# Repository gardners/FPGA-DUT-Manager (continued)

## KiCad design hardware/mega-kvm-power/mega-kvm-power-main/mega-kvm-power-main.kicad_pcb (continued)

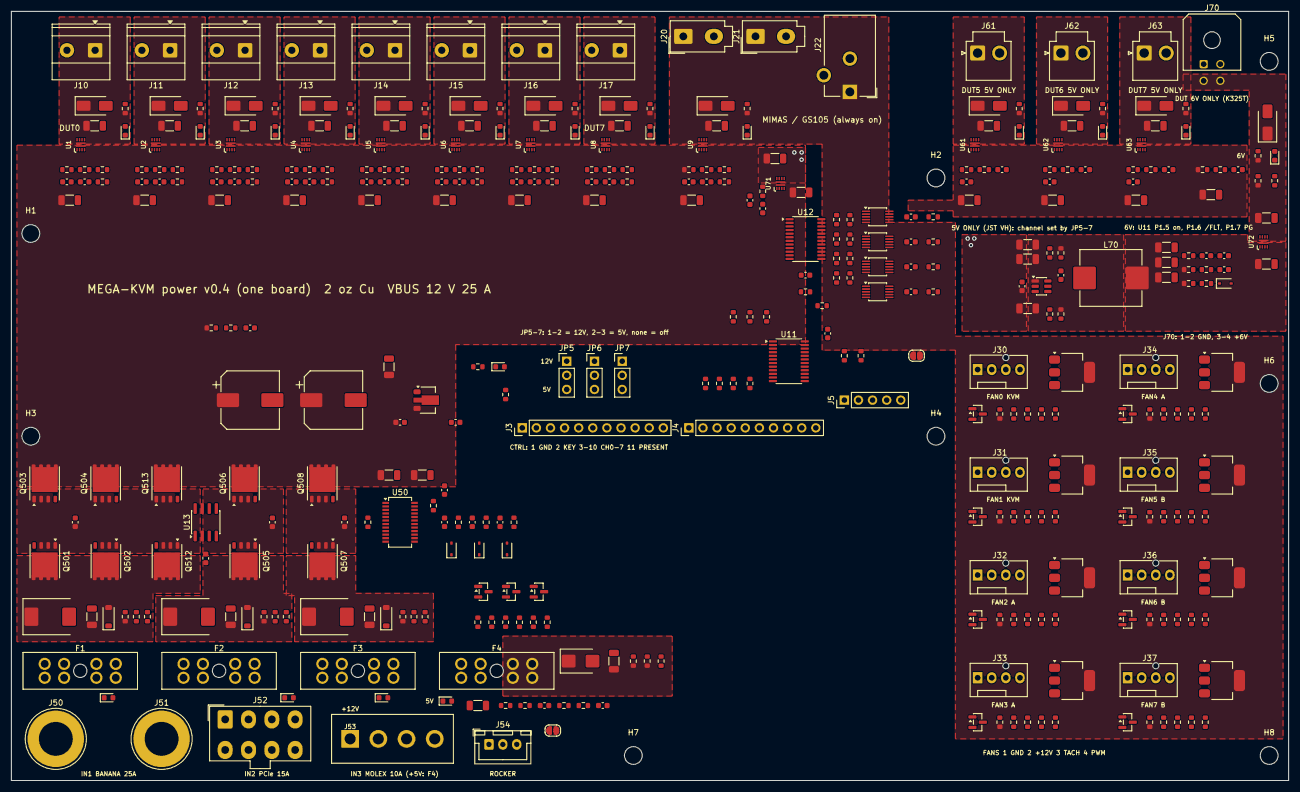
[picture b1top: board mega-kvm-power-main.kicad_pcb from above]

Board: 2 copper layers, 230.0 x 138.5 mm, 403 parts (0 on the bottom side), 228 nets, no tracks yet.

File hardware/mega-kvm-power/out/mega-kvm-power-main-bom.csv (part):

"Refs","Value","Footprint","LCSC","MPN","Qty","DNP"
"C1,C2","470u 25V","Capacitor_SMD:CP_Elec_10x10","TBD (470uF 25V 10x10 SMD)","","2",""
"C3,C504,C505,C600,C601","10u","Capacitor_SMD:C_1206_3216Metric","TBD (X7R 25V)","","5",""
"C4,C507,C514,C515,C516","1u","Capacitor_SMD:C_0603_1608Metric","TBD (X7R 50V)","","5",""
"C5","1u","Capacitor_SMD:C_0603_1608Metric","TBD (X7R 16V)","","1",""
"C6,C7,C400,C401,C402,C403,C404,C405,C506,C602,C723,C724,C732","100n","Capacitor_SMD:C_0603_1608Metric","C14663","","13",""
"C100,C110,C120,C130,C140,C150,C160,C170,C180,C610,C620,C630,C710,C730","2n2","Capacitor_SMD:C_0603_1608Metric","TBD (X7R 50V)","","14",""
"C101,C111,C121,C131,C141,C151,C161,C171,C181,C611,C621,C631,C711,C731","4n7","Capacitor_SMD:C_0603_1608Metric","TBD (X7R 50V)","","14",""
"C102,C103,C112,C113,C122,C123,C132,C133,C142,C143,C152,C153,C162,C163,C172,C173,C182,C183,C501,C502,C503,C612,C613,C622,C623,C632,C633,C712,C713,C733,C734","1u","Capacitor_SMD:C_1206_3216Metric","TBD (X7R 50V)","","31",""
"C511,C512,C513","22n","Capacitor_SMD:C_0603_1608Metric","TBD (X7R 50V)","","3",""
"C517","10n","Capacitor_SMD:C_0603_1608Metric","TBD (X7R 50V)","","1",""
"C720,C721,C722","10u","Capacitor_SMD:C_1206_3216Metric","C13585","Samsung CL31A106KBHNNNE 10 uF 50 V X5R 1206 (JLC basic)","3",""
"C725,C726,C727","22u","Capacitor_SMD:C_1206_3216Metric","C12891","Samsung CL31A226KAHNNNE 22 uF 25 V X5R 1206 (JLC basic)","3",""
"D1,D101,D111,D121,D131,D141,D151,D161,D171,D181,D507,D508,D509,D601,D611,D621,D631,D741","green","LED_SMD:LED_0603_1608Metric","TBD (0603 green, JLC basic)","","18",""
"D100,D110,D120,D130,D140,D150,D160,D170,D180,D610,D620,D630,D740","SS34","Diode_SMD:D_SMA","C8678","SS34 40 V 3 A SMA","13",""
"D501,D502,D503","SMCJ15A","Diode_SMD:D_SMC","C2834490","MDD SMCJ15A 1500 W, Vrwm 15 V, Vc 24.4 V","3",""
"D504,D505,D506","B5819W","Diode_SMD:D_SOD-123","C8598","B5819W 40 V 1 A SOD-123","3",""
"D510,D511,D512","BAT54WS","Diode_SMD:D_SOD-323","C124205","Diodes BAT54WS-7-F 30 V 0.2 A Schottky SOD-323","3",""
"D600","SMBJ5.0A","Diode_SMD:D_SMB","C2758500","SMBJ5.0A 600 W, Vrwm 5.0 V, Vbr 6.4 V min, Vc 9.2 V (issue 0055)","1",""
"D730","1N4148WS","Diode_SMD:D_SOD-323","C2128","1N4148WS 100 V 150 mA SOD-323 (JLC basic); silicon, not Schottky: its reverse leakage into EN6O stays < 0.5 uA hot","1",""
"F1","25A ATO","Fuse:FuseHolder_Blade_ATO_Littelfuse_FLR_178.6165","TBD","Littelfuse 178.6165.0002 ATO PCB holder + ATO blade fuse 25A ATO","1",""
"F2","15A ATO","Fuse:FuseHolder_Blade_ATO_Littelfuse_FLR_178.6165","TBD","Littelfuse 178.6165.0002 ATO PCB holder + ATO blade fuse 15A ATO","1",""
"F3,F4","10A ATO","Fuse:FuseHolder_Blade_ATO_Littelfuse_FLR_178.6165","TBD","Littelfuse 178.6165.0002 ATO PCB holder + ATO blade fuse 10 A (same as F3),Littelfuse 178.6165.0002 ATO PCB holder + ATO blade fuse 10A ATO","2",""
"J3","CTRL 1x11 key2","Connector_PinHeader_2.54mm:PinHeader_1x11_P2.54mm_Vertical","TBD (2.54 mm 1x11 header)","","1",""
"J4","STATUS 1x10","Connector_PinHeader_2.54mm:PinHeader_1x10_P2.54mm_Vertical","TBD (2.54 mm 1x10 header)","","1",""
"J5","I2C 1x5","Connector_PinHeader_2.54mm:PinHeader_1x05_P2.54mm_Vertical","TBD","","1",""
"J10","DUT0 12V","TerminalBlock_Phoenix:TerminalBlock_Phoenix_MKDS-1,5-2-5.08_1x02_P5.08mm_Horizontal","TBD: JLC-stocked KF128/DG128-5.08-2P clone (THT, machine/wave assembled)","2-pole 5.08 mm PCB screw terminal, MKDS 1,5/2-5,08 class (13.5 A); pin 1 = + (OUTn), pin 2 = - (GND)","1",""
"J11","DUT1 12V","TerminalBlock_Phoenix:TerminalBlock_Phoenix_MKDS-1,5-2-5.08_1x02_P5.08mm_Horizontal","TBD: JLC-stocked KF128/DG128-5.08-2P clone (THT, machine/wave assembled)","2-pole 5.08 mm PCB screw terminal, MKDS 1,5/2-5,08 class (13.5 A); pin 1 = + (OUTn), pin 2 = - (GND)","1",""
"J12","DUT2 12V","TerminalBlock_Phoenix:TerminalBlock_Phoenix_MKDS-1,5-2-5.08_1x02_P5.08mm_Horizontal","TBD: JLC-stocked KF128/DG128-5.08-2P clone (THT, machine/wave assembled)","2-pole 5.08 mm PCB screw terminal, MKDS 1,5/2-5,08 class (13.5 A); pin 1 = + (OUTn), pin 2 = - (GND)","1",""
"J13","DUT3 12V","TerminalBlock_Phoenix:TerminalBlock_Phoenix_MKDS-1,5-2-5.08_1x02_P5.08mm_Horizontal","TBD: JLC-stocked KF128/DG128-5.08-2P clone (THT, machine/wave assembled)","2-pole 5.08 mm PCB screw terminal, MKDS 1,5/2-5,08 class (13.5 A); pin 1 = + (OUTn), pin 2 = - (GND)","1",""
"J14","DUT4 12V","TerminalBlock_Phoenix:TerminalBlock_Phoenix_MKDS-1,5-2-5.08_1x02_P5.08mm_Horizontal","TBD: JLC-stocked KF128/DG128-5.08-2P clone (THT, machine/wave assembled)","2-pole 5.08 mm PCB screw terminal, MKDS 1,5/2-5,08 class (13.5 A); pin 1 = + (OUTn), pin 2 = - (GND)","1",""
"J15","DUT5 12V","TerminalBlock_Phoenix:TerminalBlock_Phoenix_MKDS-1,5-2-5.08_1x02_P5.08mm_Horizontal","TBD: JLC-stocked KF128/DG128-5.08-2P clone (THT, machine/wave assembled)","2-pole 5.08 mm PCB screw terminal, MKDS 1,5/2-5,08 class (13.5 A); pin 1 = + (OUTn), pin 2 = - (GND)","1",""
"J16","DUT6 12V","TerminalBlock_Phoenix:TerminalBlock_Phoenix_MKDS-1,5-2-5.08_1x02_P5.08mm_Horizontal","TBD: JLC-stocked KF128/DG128-5.08-2P clone (THT, machine/wave assembled)","2-pole 5.08 mm PCB screw terminal, MKDS 1,5/2-5,08 class (13.5 A); pin 1 = + (OUTn), pin 2 = - (GND)","1",""
"J17","DUT7 12V","TerminalBlock_Phoenix:TerminalBlock_Phoenix_MKDS-1,5-2-5.08_1x02_P5.08mm_Horizontal","TBD: JLC-stocked KF128/DG128-5.08-2P clone (THT, machine/wave assembled)","2-pole 5.08 mm PCB screw terminal, MKDS 1,5/2-5,08 class (13.5 A); pin 1 = + (OUTn), pin 2 = - (GND)","1",""
"J20","MIMAS0 12V","Connector_Molex:Molex_Mini-Fit_Jr_5566-02A_2x01_P4.20mm_Vertical","TBD","Molex 39-28-1023 (5566-02A) Mini-Fit Jr 2-pin vertical, 9 A","1",""
"J21","MIMAS1 12V","Connector_Molex:Molex_Mini-Fit_Jr_5566-02A_2x01_P4.20mm_Vertical","TBD","Molex 39-28-1023 (5566-02A) Mini-Fit Jr 2-pin vertical, 9 A","1",""
"J22","GS105 12V","Connector_BarrelJack:BarrelJack_CUI_PJ-102AH_Horizontal","TBD","CUI PJ-102AH 2.1 mm, 2.5 A","1",""
"J30","FAN0","Connector:FanPinHeader_1x04_P2.54mm_Vertical","C240840","Molex 47053-1000 4-pin PWM fan header","1",""
"J31","FAN1","Connector:FanPinHeader_1x04_P2.54mm_Vertical","C240840","Molex 47053-1000 4-pin PWM fan header","1",""
"J32","FAN2","Connector:FanPinHeader_1x04_P2.54mm_Vertical","C240840","Molex 47053-1000 4-pin PWM fan header","1",""
"J33","FAN3","Connector:FanPinHeader_1x04_P2.54mm_Vertical","C240840","Molex 47053-1000 4-pin PWM fan header","1",""
"J34","FAN4","Connector:FanPinHeader_1x04_P2.54mm_Vertical","C240840","Molex 47053-1000 4-pin PWM fan header","1",""
"J35","FAN5","Connector:FanPinHeader_1x04_P2.54mm_Vertical","C240840","Molex 47053-1000 4-pin PWM fan header","1",""
"J36","FAN6","Connector:FanPinHeader_1x04_P2.54mm_Vertical","C240840","Molex 47053-1000 4-pin PWM fan header","1",""
"J37","FAN7","Connector:FanPinHeader_1x04_P2.54mm_Vertical","C240840","Molex 47053-1000 4-pin PWM fan header","1",""
"J50","BANANA +12V (red)","Connector:Banana_Jack_1Pin","C7437321","4 mm PCB-mount banana socket, red, 24 A (e.g. 24.243.1, THT; CHECK the footprint against the chosen part)","1",""
"J51","BANANA GND (black)","Connector:Banana_Jack_1Pin","C7437322","4 mm PCB-mount banana socket, black, 24 A (e.g. 24.243.2, THT; CHECK the footprint against the chosen part)","1",""
"J52","PCIe 8-pin","Connector_Molex:Molex_Mini-Fit_Jr_5566-08A_2x04_P4.20mm_Vertical","TBD (JLC-stocked Mini-Fit 2x4 vertical)","Molex Mini-Fit Jr 8-pin vertical header with PCIe keying (45558-series or 39-28-1083 + check keying); pins 1-3 +12 V, 4-8 GND (sense pins grounded)","1",""
"J53","Molex 4-pin","mega-kvm-power:Molex_8981_PeripheralPower_1x04_P5.08mm_Vertical","TBD","Molex 8981 4-pin male PCB header, vertical (e.g. 15-24-4048); 1 +12 V, 2-3 GND, 4 +5 V (to F4 and the 5 V outputs, issue 0055)","1",""
"J54","MASTER SW","Connector_JST:JST_XH_B3B-XH-A_1x03_P2.50mm_Vertical","C144395 (verify)","JST B3B-XH-A","1",""
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
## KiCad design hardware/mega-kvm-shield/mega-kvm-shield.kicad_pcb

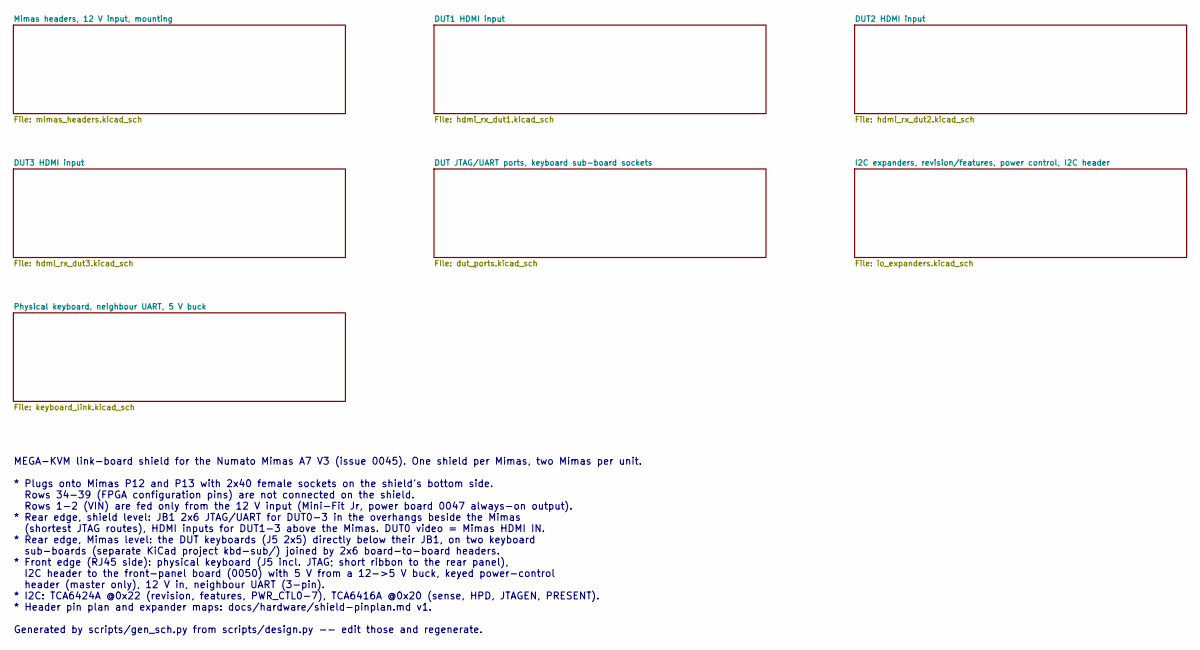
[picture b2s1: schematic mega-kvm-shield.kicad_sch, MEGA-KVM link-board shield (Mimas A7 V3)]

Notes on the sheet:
MEGA-KVM link-board shield for the Numato Mimas A7 V3 (issue 0045). One shield per Mimas, two Mimas per unit. * Plugs onto Mimas P12 and P13 with 2x40 female sockets on the shield's bottom side. Rows 34-39 (FPGA configuration pins) are not connected on the shield. Rows 1-2 (VIN) are fed only from t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

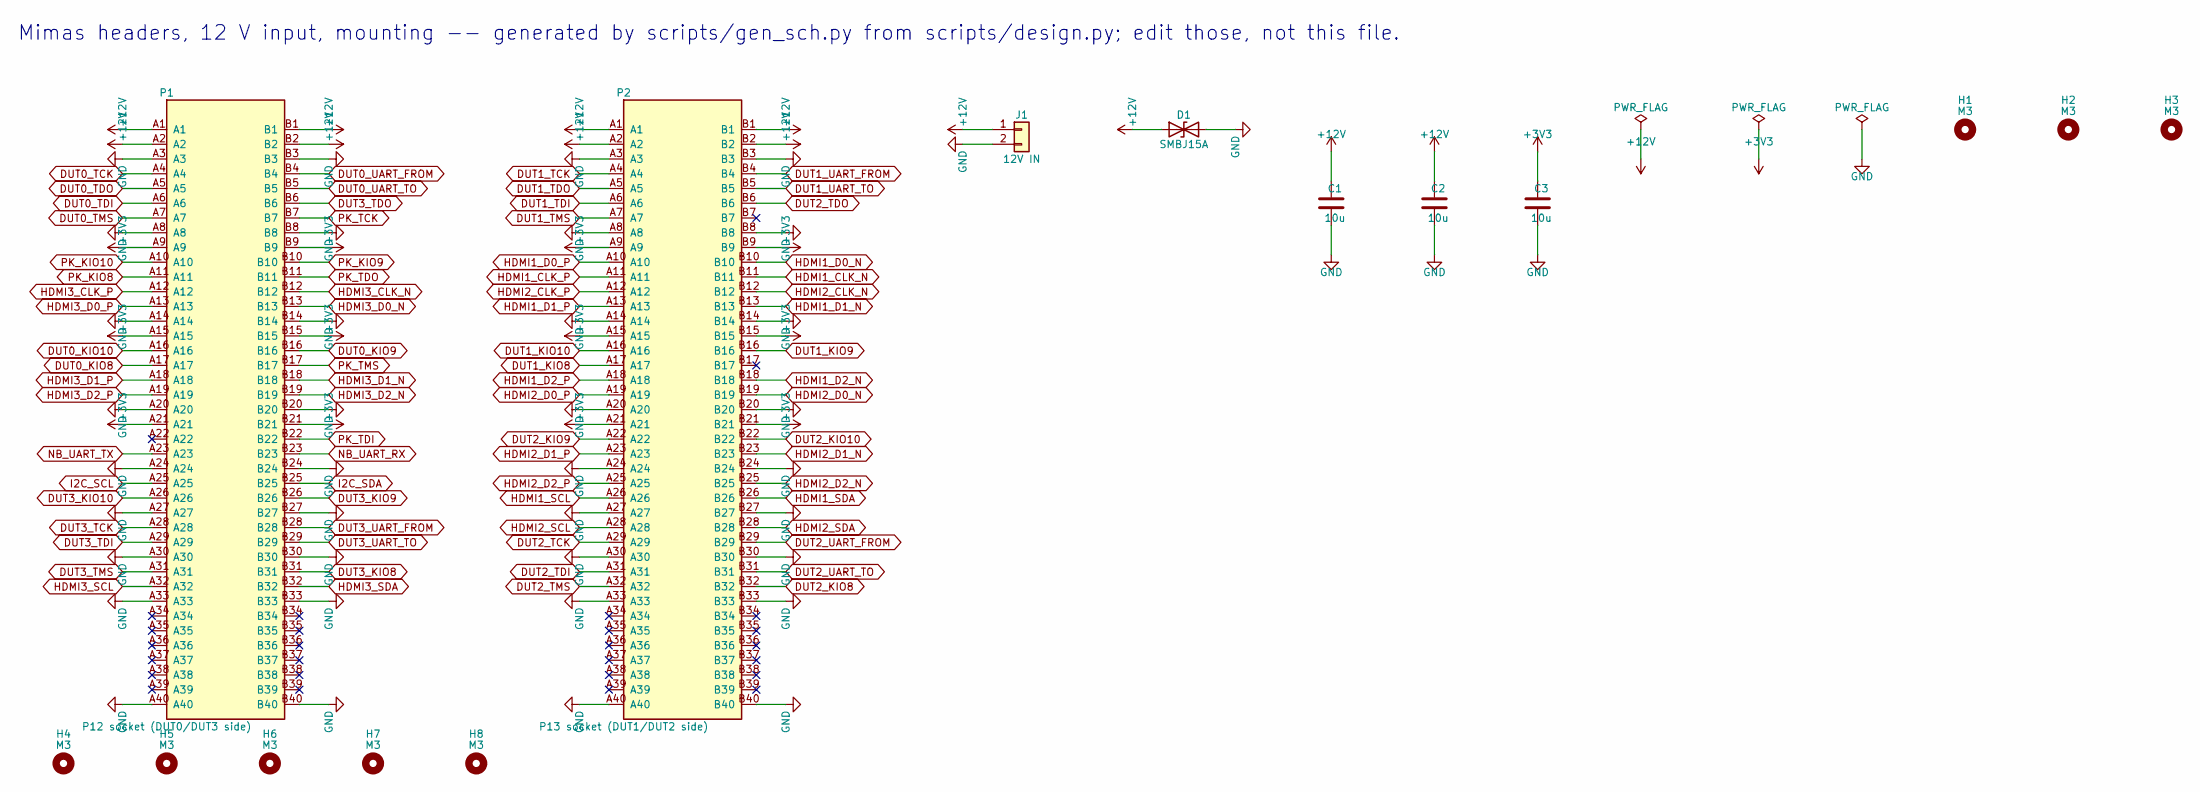
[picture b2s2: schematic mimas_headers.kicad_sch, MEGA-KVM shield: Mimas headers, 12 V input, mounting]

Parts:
C1, C2: 10u; C_1206_3216Metric
C3: 10u; C_0805_2012Metric; LCSC C15850
D1: SMBJ15A; D_SMB
H1, H2, H3, H4, H5, H6, H7, H8: M3; MountingHole_3.2mm_M3
J1: 12V IN; Molex_Mini-Fit_Jr_5566-02A_2x01_P4.20mm_Vertical; MPN Molex 5566-02A (39-30-1020 class)
P1: P12 socket (DUT0/DUT3 side); Mimas_Header_Socket_2x40
P2: P13 socket (DUT1/DUT2 side); Mimas_Header_Socket_2x40

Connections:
+3V3: C3.1, P1.A9, P1.A15, P1.A21, P1.B9, P1.B15, P1.B21, P2.A9, P2.A15, P2.A21, P2.B9, P2.B15, P2.B21; also elsewhere on the board
+12V: C1.1, C2.1, D1.1 (A1), J1.1, P1.A1, P1.A2, P1.B1, P1.B2, P2.A1, P2.A2, P2.B1, P2.B2; also elsewhere on the board
DUT0_KIO8: P1.A17; also elsewhere on the board
DUT0_KIO9: P1.B16; also elsewhere on the board
DUT0_KIO10: P1.A16; also elsewhere on the board
DUT0_TCK: P1.A4; also elsewhere on the board
DUT0_TDI: P1.A6; also elsewhere on the board
DUT0_TDO: P1.A5; also elsewhere on the board
DUT0_TMS: P1.A7; also elsewhere on the board
DUT0_UART_FROM: P1.B4; also elsewhere on the board
DUT0_UART_TO: P1.B5; also elsewhere on the board
DUT1_KIO8: P2.A17; also elsewhere on the board
DUT1_KIO9: P2.B16; also elsewhere on the board
DUT1_KIO10: P2.A16; also elsewhere on the board
DUT1_TCK: P2.A4; also elsewhere on the board
DUT1_TDI: P2.A6; also elsewhere on the board
DUT1_TDO: P2.A5; also elsewhere on the board
DUT1_TMS: P2.A7; also elsewhere on the board
DUT1_UART_FROM: P2.B4; also elsewhere on the board
DUT1_UART_TO: P2.B5; also elsewhere on the board
DUT2_KIO8: P2.B32; also elsewhere on the board
DUT2_KIO9: P2.A22; also elsewhere on the board
DUT2_KIO10: P2.B22; also elsewhere on the board
DUT2_TCK: P2.A29; also elsewhere on the board
DUT2_TDI: P2.A31; also elsewhere on the board
DUT2_TDO: P2.B6; also elsewhere on the board
DUT2_TMS: P2.A32; also elsewhere on the board
DUT2_UART_FROM: P2.B29; also elsewhere on the board
DUT2_UART_TO: P2.B31; also elsewhere on the board
DUT3_KIO8: P1.B31; also elsewhere on the board
DUT3_KIO9: P1.B26; also elsewhere on the board
DUT3_KIO10: P1.A26; also elsewhere on the board
DUT3_TCK: P1.A28; also elsewhere on the board
DUT3_TDI: P1.A29; also elsewhere on the board
DUT3_TDO: P1.B6; also elsewhere on the board
DUT3_TMS: P1.A31; also elsewhere on the board
DUT3_UART_FROM: P1.B28; also elsewhere on the board
DUT3_UART_TO: P1.B29; also elsewhere on the board
GND: C1.2, C2.2, C3.2, D1.2 (A2), J1.2, P1.A3, P1.A8, P1.A14, P1.A20, P1.A24, P1.A27, P1.A30, P1.A33, P1.A40, P1.B3, P1.B8, P1.B14, P1.B20, P1.B24, P1.B27, P1.B30, P1.B33, P1.B40, P2.A3, P2.A8, P2.A14, P2.A20, P2.A24, P2.A27, P2.A30, P2.A33, P2.A40, P2.B3, P2.B8, P2.B14, P2.B20, P2.B24, P2.B27, P2.B30, P2.B33, P2.B40; also elsewhere on the board
HDMI1_CLK_N: P2.B11; also elsewhere on the board
HDMI1_CLK_P: P2.A11; also elsewhere on the board
HDMI1_D0_N: P2.B10; also elsewhere on the board
HDMI1_D0_P: P2.A10; also elsewhere on the board
HDMI1_D1_N: P2.B13; also elsewhere on the board
HDMI1_D1_P: P2.A13; also elsewhere on the board
HDMI1_D2_N: P2.B18; also elsewhere on the board
HDMI1_D2_P: P2.A18; also elsewhere on the board
HDMI1_SCL: P2.A26; also elsewhere on the board
HDMI1_SDA: P2.B26; also elsewhere on the board
HDMI2_CLK_N: P2.B12; also elsewhere on the board
HDMI2_CLK_P: P2.A12; also elsewhere on the board
HDMI2_D0_N: P2.B19; also elsewhere on the board
HDMI2_D0_P: P2.A19; also elsewhere on the board
HDMI2_D1_N: P2.B23; also elsewhere on the board
HDMI2_D1_P: P2.A23; also elsewhere on the board
HDMI2_D2_N: P2.B25; also elsewhere on the board
HDMI2_D2_P: P2.A25; also elsewhere on the board
HDMI2_SCL: P2.A28; also elsewhere on the board
HDMI2_SDA: P2.B28; also elsewhere on the board
HDMI3_CLK_N: P1.B12; also elsewhere on the board
HDMI3_CLK_P: P1.A12; also elsewhere on the board
HDMI3_D0_N: P1.B13; also elsewhere on the board
HDMI3_D0_P: P1.A13; also elsewhere on the board
HDMI3_D1_N: P1.B18; also elsewhere on the board
HDMI3_D1_P: P1.A18; also elsewhere on the board
HDMI3_D2_N: P1.B19; also elsewhere on the board
HDMI3_D2_P: P1.A19; also elsewhere on the board
HDMI3_SCL: P1.A32; also elsewhere on the board
HDMI3_SDA: P1.B32; also elsewhere on the board
I2C_SCL: P1.A25; also elsewhere on the board
I2C_SDA: P1.B25; also elsewhere on the board
NB_UART_RX: P1.B23; also elsewhere on the board
NB_UART_TX: P1.A23; also elsewhere on the board
PK_KIO8: P1.A11; also elsewhere on the board
PK_KIO9: P1.B10; also elsewhere on the board
PK_KIO10: P1.A10; also elsewhere on the board
PK_TCK: P1.B7; also elsewhere on the board
PK_TDI: P1.B22; also elsewhere on the board
PK_TDO: P1.B11; also elsewhere on the board
PK_TMS: P1.B17; also elsewhere on the board

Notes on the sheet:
Mimas headers, 12 V input, mounting -- generated by scripts/gen_sch.py from scripts/design.py; edit those, not this file.

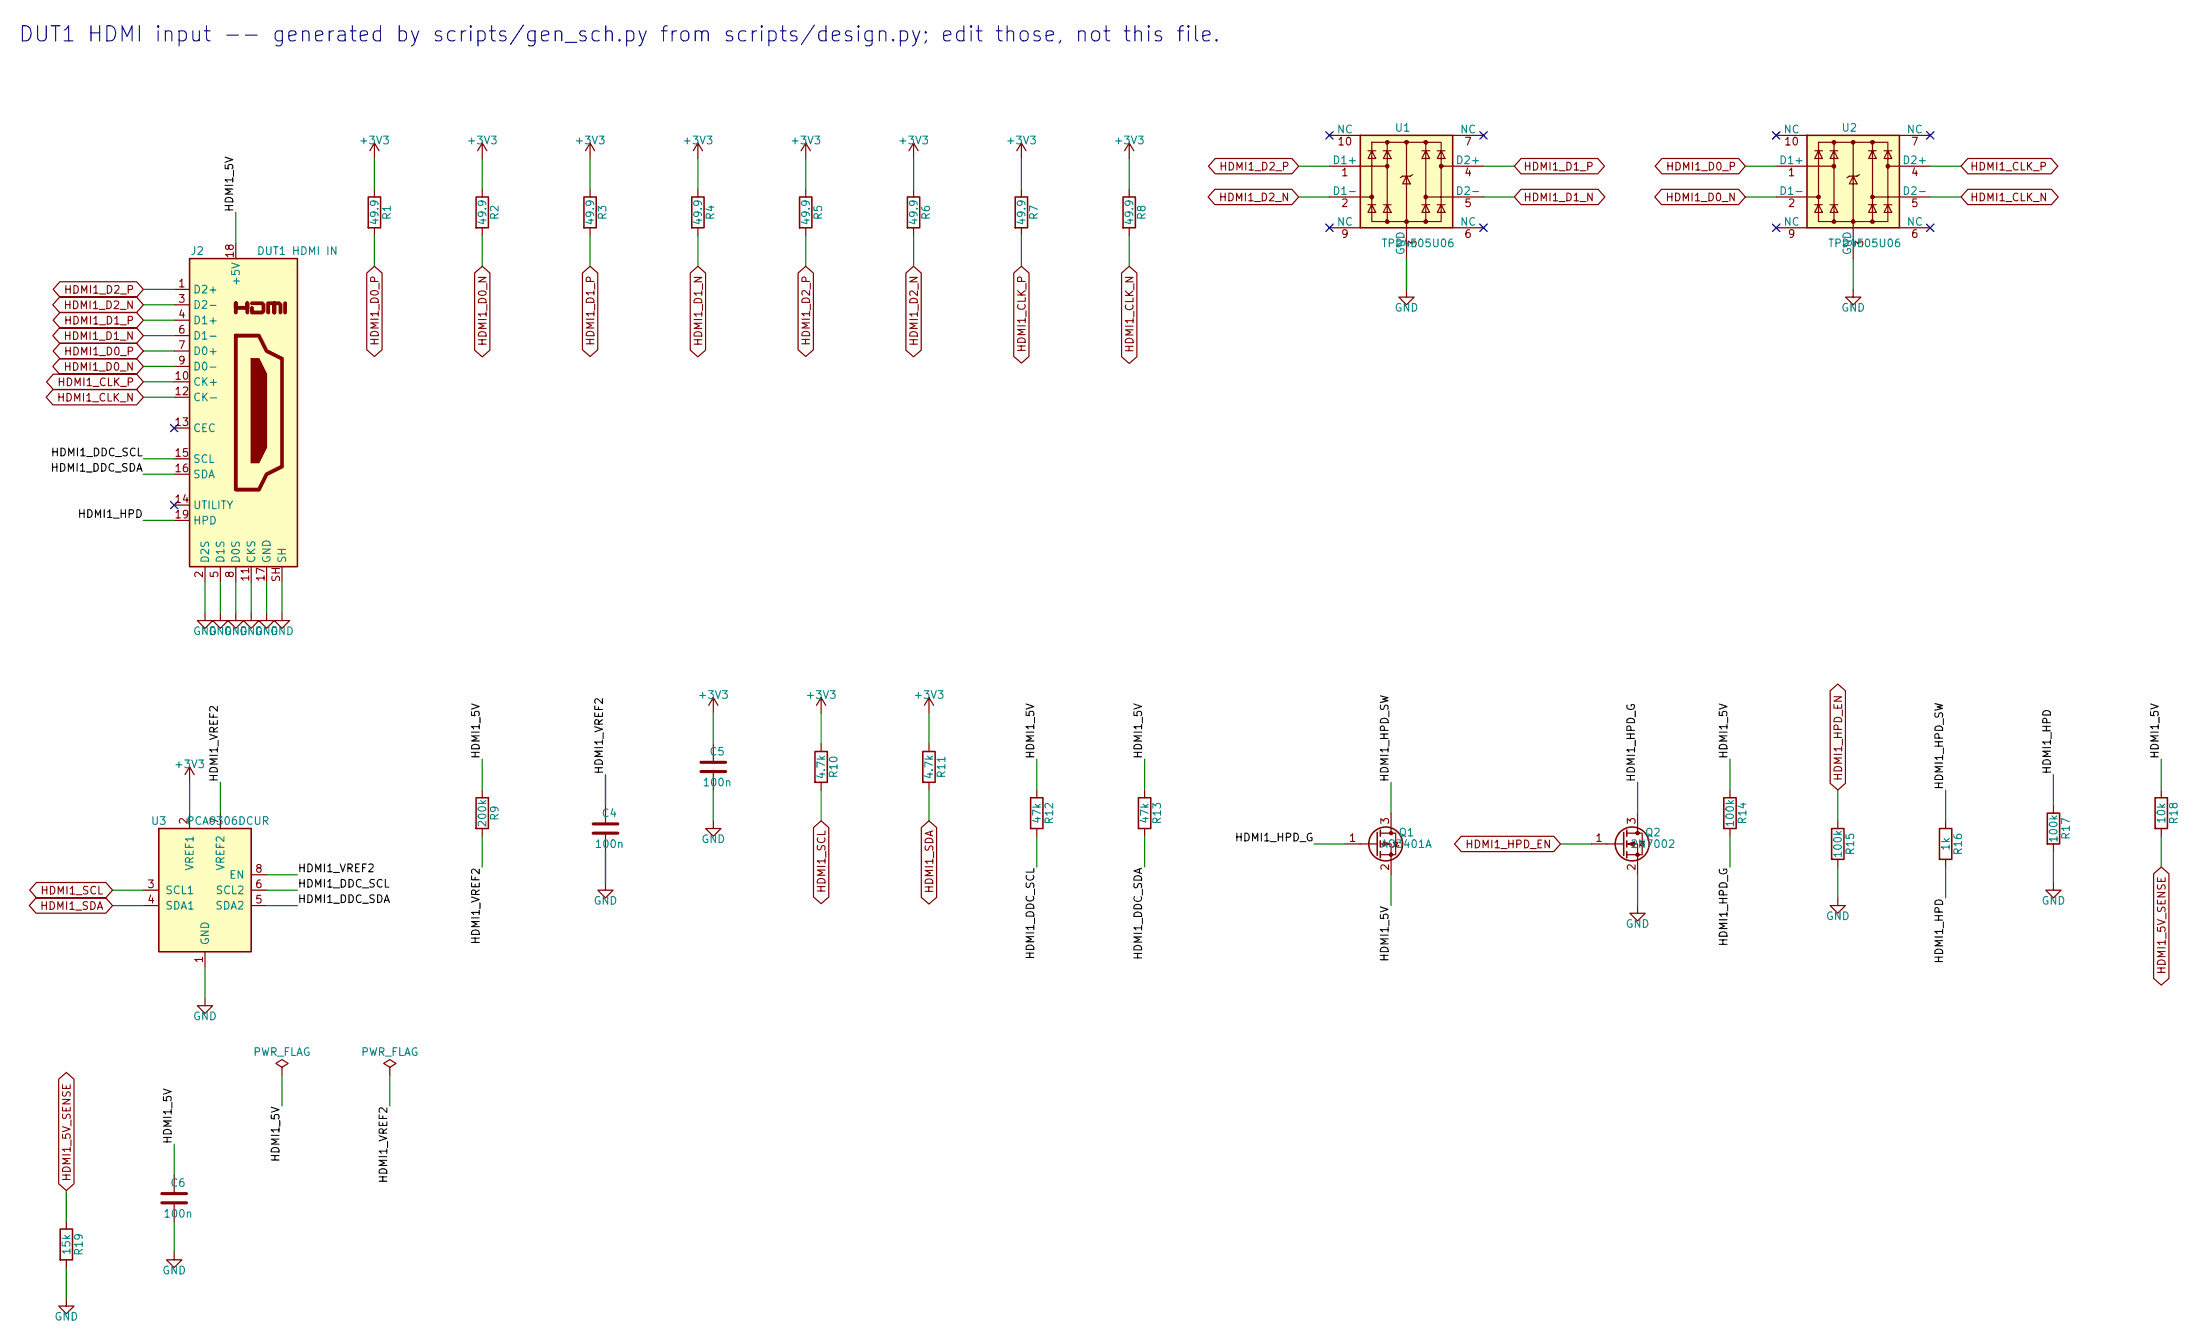
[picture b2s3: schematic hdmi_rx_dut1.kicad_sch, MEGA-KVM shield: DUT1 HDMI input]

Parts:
C4, C5, C6: 100n; C_0402_1005Metric; LCSC C1525
J2: DUT1 HDMI IN; HDMI_A_Amphenol_10029449-x01xLF_Horizontal; MPN Amphenol 10029449-111RLF
Q1: AO3401A; SOT-23; LCSC C15127
Q2: 2N7002; SOT-23; LCSC C8545
R1, R2, R3, R4, R5, R6, R7, R8: 49.9; R_0402_1005Metric; LCSC C25120
R9: 200k; R_0402_1005Metric; LCSC C25811
R10, R11: 4.7k; R_0402_1005Metric; LCSC C25900
R12, R13: 47k; R_0402_1005Metric; LCSC C25792
R14, R15, R17: 100k; R_0402_1005Metric; LCSC C25741
R16: 1k; R_0402_1005Metric; LCSC C11702
R18: 10k; R_0402_1005Metric; LCSC C25744
R19: 15k; R_0402_1005Metric; LCSC C25756
U1, U2: TPD4E05U06; USON-10_2.5x1.0mm_P0.5mm; LCSC C138714
U3: PCA9306DCUR; VSSOP-8_2.3x2mm_P0.5mm

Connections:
+3V3: C5.1, R1.1, R2.1, R3.1, R4.1, R5.1, R6.1, R7.1, R8.1, R10.1, R11.1, U3.2 (VREF1); also elsewhere on the board
GND: C4.2, C5.2, C6.2, J2.2 (D2S), J2.5 (D1S), J2.8 (D0S), J2.11 (CKS), J2.17 (GND), J2.SH, Q2.2 (S), R15.2, R17.2, R19.2, U1.3 (GND), U1.8 (GND), U2.3 (GND), U2.8 (GND), U3.1 (GND); also elsewhere on the board
HDMI1_5V: C6.1, J2.18 (+5V), Q1.2 (S), R9.1, R12.1, R13.1, R14.1, R18.1
HDMI1_5V_SENSE: R18.2, R19.1; also elsewhere on the board
HDMI1_CLK_N: J2.12 (CK-), R8.2, U2.5 (D2-); also elsewhere on the board
HDMI1_CLK_P: J2.10 (CK+), R7.2, U2.4 (D2+); also elsewhere on the board
HDMI1_D0_N: J2.9 (D0-), R2.2, U2.2 (D1-); also elsewhere on the board
HDMI1_D0_P: J2.7 (D0+), R1.2, U2.1 (D1+); also elsewhere on the board
HDMI1_D1_N: J2.6 (D1-), R4.2, U1.5 (D2-); also elsewhere on the board
HDMI1_D1_P: J2.4 (D1+), R3.2, U1.4 (D2+); also elsewhere on the board
HDMI1_D2_N: J2.3 (D2-), R6.2, U1.2 (D1-); also elsewhere on the board
HDMI1_D2_P: J2.1 (D2+), R5.2, U1.1 (D1+); also elsewhere on the board
HDMI1_DDC_SCL: J2.15 (SCL), R12.2, U3.6 (SCL2)
HDMI1_DDC_SDA: J2.16 (SDA), R13.2, U3.5 (SDA2)
HDMI1_HPD: J2.19 (HPD), R16.2, R17.1
HDMI1_HPD_EN: Q2.1 (G), R15.1; also elsewhere on the board
HDMI1_HPD_G: Q1.1 (G), Q2.3 (D), R14.2
HDMI1_HPD_SW: Q1.3 (D), R16.1
HDMI1_SCL: R10.2, U3.3 (SCL1); also elsewhere on the board
HDMI1_SDA: R11.2, U3.4 (SDA1); also elsewhere on the board
HDMI1_VREF2: C4.1, R9.2, U3.7 (VREF2), U3.8 (EN)

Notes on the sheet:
DUT1 HDMI input -- generated by scripts/gen_sch.py from scripts/design.py; edit those, not this file.

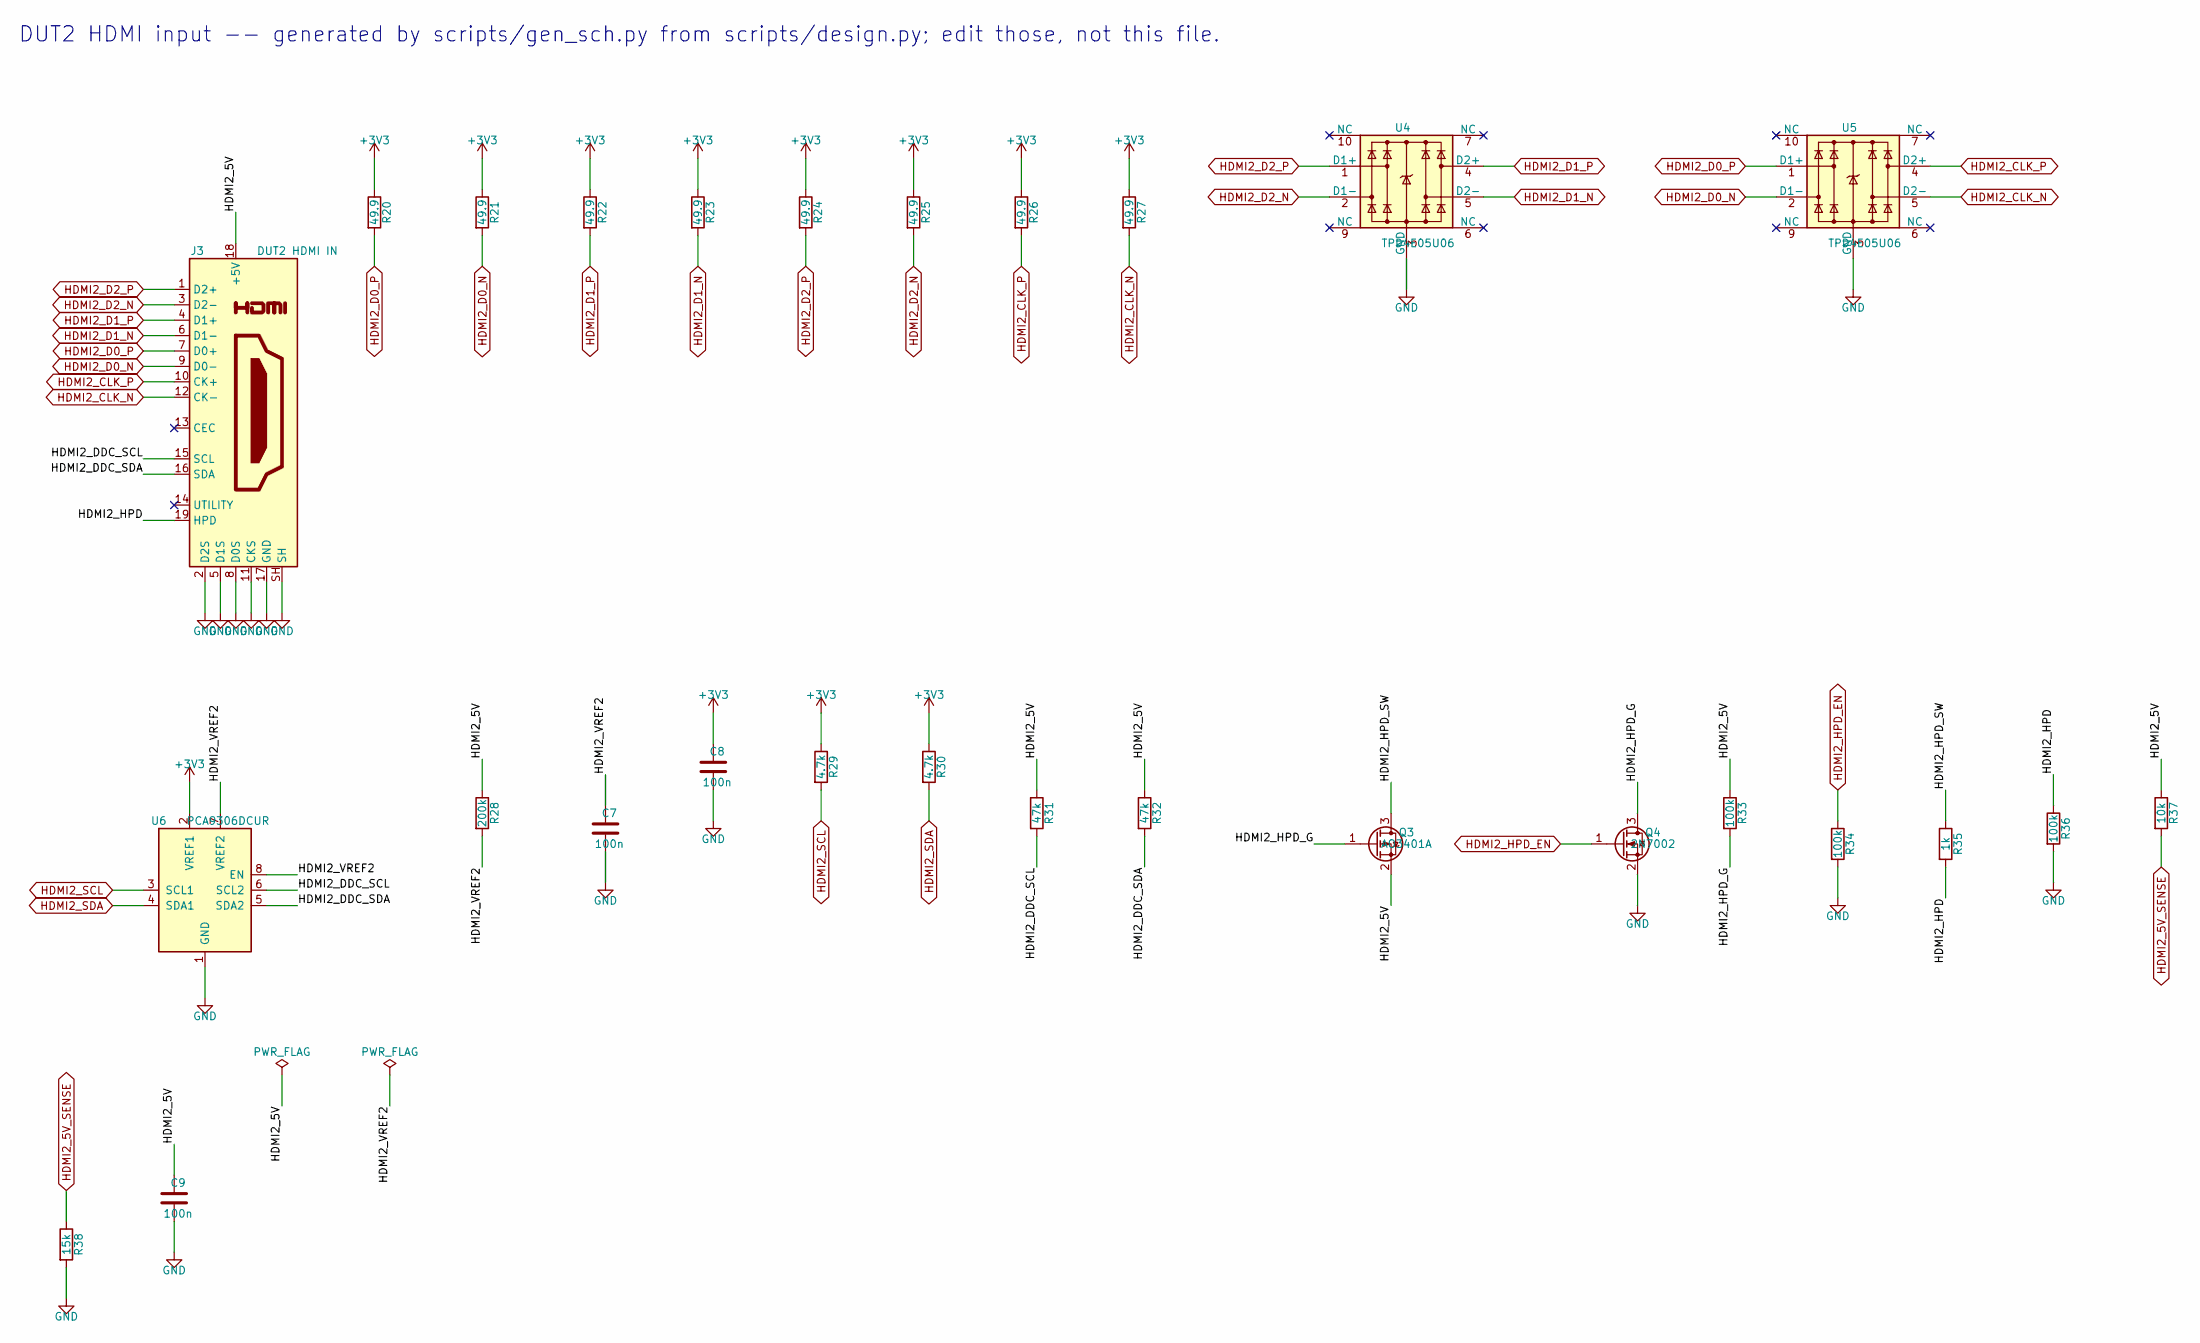
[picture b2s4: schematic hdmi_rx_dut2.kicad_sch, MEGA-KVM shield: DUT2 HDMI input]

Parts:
C7, C8, C9: 100n; C_0402_1005Metric; LCSC C1525
J3: DUT2 HDMI IN; HDMI_A_Amphenol_10029449-x01xLF_Horizontal; MPN Amphenol 10029449-111RLF
Q3: AO3401A; SOT-23; LCSC C15127
Q4: 2N7002; SOT-23; LCSC C8545
R20, R21, R22, R23, R24, R25, R26, R27: 49.9; R_0402_1005Metric; LCSC C25120
R28: 200k; R_0402_1005Metric; LCSC C25811
R29, R30: 4.7k; R_0402_1005Metric; LCSC C25900
R31, R32: 47k; R_0402_1005Metric; LCSC C25792
R33, R34, R36: 100k; R_0402_1005Metric; LCSC C25741
R35: 1k; R_0402_1005Metric; LCSC C11702
R37: 10k; R_0402_1005Metric; LCSC C25744
R38: 15k; R_0402_1005Metric; LCSC C25756
U4, U5: TPD4E05U06; USON-10_2.5x1.0mm_P0.5mm; LCSC C138714
U6: PCA9306DCUR; VSSOP-8_2.3x2mm_P0.5mm

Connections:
+3V3: C8.1, R20.1, R21.1, R22.1, R23.1, R24.1, R25.1, R26.1, R27.1, R29.1, R30.1, U6.2 (VREF1); also elsewhere on the board
GND: C7.2, C8.2, C9.2, J3.2 (D2S), J3.5 (D1S), J3.8 (D0S), J3.11 (CKS), J3.17 (GND), J3.SH, Q4.2 (S), R34.2, R36.2, R38.2, U4.3 (GND), U4.8 (GND), U5.3 (GND), U5.8 (GND), U6.1 (GND); also elsewhere on the board
HDMI2_5V: C9.1, J3.18 (+5V), Q3.2 (S), R28.1, R31.1, R32.1, R33.1, R37.1
HDMI2_5V_SENSE: R37.2, R38.1; also elsewhere on the board
HDMI2_CLK_N: J3.12 (CK-), R27.2, U5.5 (D2-); also elsewhere on the board
HDMI2_CLK_P: J3.10 (CK+), R26.2, U5.4 (D2+); also elsewhere on the board
HDMI2_D0_N: J3.9 (D0-), R21.2, U5.2 (D1-); also elsewhere on the board
HDMI2_D0_P: J3.7 (D0+), R20.2, U5.1 (D1+); also elsewhere on the board
HDMI2_D1_N: J3.6 (D1-), R23.2, U4.5 (D2-); also elsewhere on the board
HDMI2_D1_P: J3.4 (D1+), R22.2, U4.4 (D2+); also elsewhere on the board
HDMI2_D2_N: J3.3 (D2-), R25.2, U4.2 (D1-); also elsewhere on the board
HDMI2_D2_P: J3.1 (D2+), R24.2, U4.1 (D1+); also elsewhere on the board
HDMI2_DDC_SCL: J3.15 (SCL), R31.2, U6.6 (SCL2)
HDMI2_DDC_SDA: J3.16 (SDA), R32.2, U6.5 (SDA2)
HDMI2_HPD: J3.19 (HPD), R35.2, R36.1
HDMI2_HPD_EN: Q4.1 (G), R34.1; also elsewhere on the board
HDMI2_HPD_G: Q3.1 (G), Q4.3 (D), R33.2
HDMI2_HPD_SW: Q3.3 (D), R35.1
HDMI2_SCL: R29.2, U6.3 (SCL1); also elsewhere on the board
HDMI2_SDA: R30.2, U6.4 (SDA1); also elsewhere on the board
HDMI2_VREF2: C7.1, R28.2, U6.7 (VREF2), U6.8 (EN)

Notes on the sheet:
DUT2 HDMI input -- generated by scripts/gen_sch.py from scripts/design.py; edit those, not this file.
